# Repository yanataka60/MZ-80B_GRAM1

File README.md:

# MZ-80B GRAM1ボード

　MZ-80B OWNER'S MANUAL p65「図4-19 グラフィックメモリ1 MZ-8BG(オプション)」回路図から基板を起こしました。

　本体への装着方法は純正品と同じです。

## 回路図
　KiCadフォルダ内のMZ-80B_GRAM1.pdf参照

[回路図](https://github.com/yanataka60/MZ-80B_GRAM1/blob/main/KiCAD/MZ-80B_GRAM1.pdf)

## 部品表
|番号|品名|数量|備考|
| ------------ | ------------ | ------------ | ------------ |
|C1|電解コンデンサ 16V100uF|1||
|C2-C6, C8-C14, C16-C20|積層セラミックコンデンサ 0.1uF|17||
|C7|コンデンサ 470pF|1||
|C15|コンデンサ 220pF|1||
|J1|2x20ピンヘッダ|1|秋月電子通商 PH-2x40SG等|
|J2|2x5ピンヘッダ|2|秋月電子通商 PH-2x40SG等|
|J3|2x5ピンヘッダ|2|GRAM2接続用 秋月電子通商 PH-2x40SG等|
|R1-R4|カーボン抵抗 1k|4||
|R5|カーボン抵抗 47Ω|1||
|R6|カーボン抵抗 100Ω|1||
|U1|8kx8 SRAM 6264|1|若松通商等|
|U5-U8|74LS157|4|若松通商等|
|U10-U12|74LS93|3|若松通商等|
|U13|74LS245|1|若松通商等|
|U14|74LS165|1|若松通商等|
|U15|74LS175|1|若松通商等|
|U16|74LS04|1|若松通商等|
|U17|74LS107|1|若松通商等|
|U18, U20|74LS32|2|若松通商等|
|U19|74LS08|1|若松通商等|
|U21|74LS00|1|若松通商等|
||2x20フラットケーブル|1|15cm程度|
||2x5フラットケーブル|1|20cm程度|

## ボードの完成写真

## 取付方法
ケーブルは1Pinの△マークを合わせて接続します。マザーボート上で2x5Pinケーブルなら手前左に1Pinの△マークがあり、2x20Pinケーブルは、右奥に1Pinの△マークがあります。

上筐体の裏側にGRAM1ボードを挿し込みます。

## 追記
2025.10.10 回路図のpdfファイルを追加した。

2025.10.15 J3は使用しないので部品表を修正。

2025.10.16 すみません。GRAM2を使うときにはJ3必要でした。

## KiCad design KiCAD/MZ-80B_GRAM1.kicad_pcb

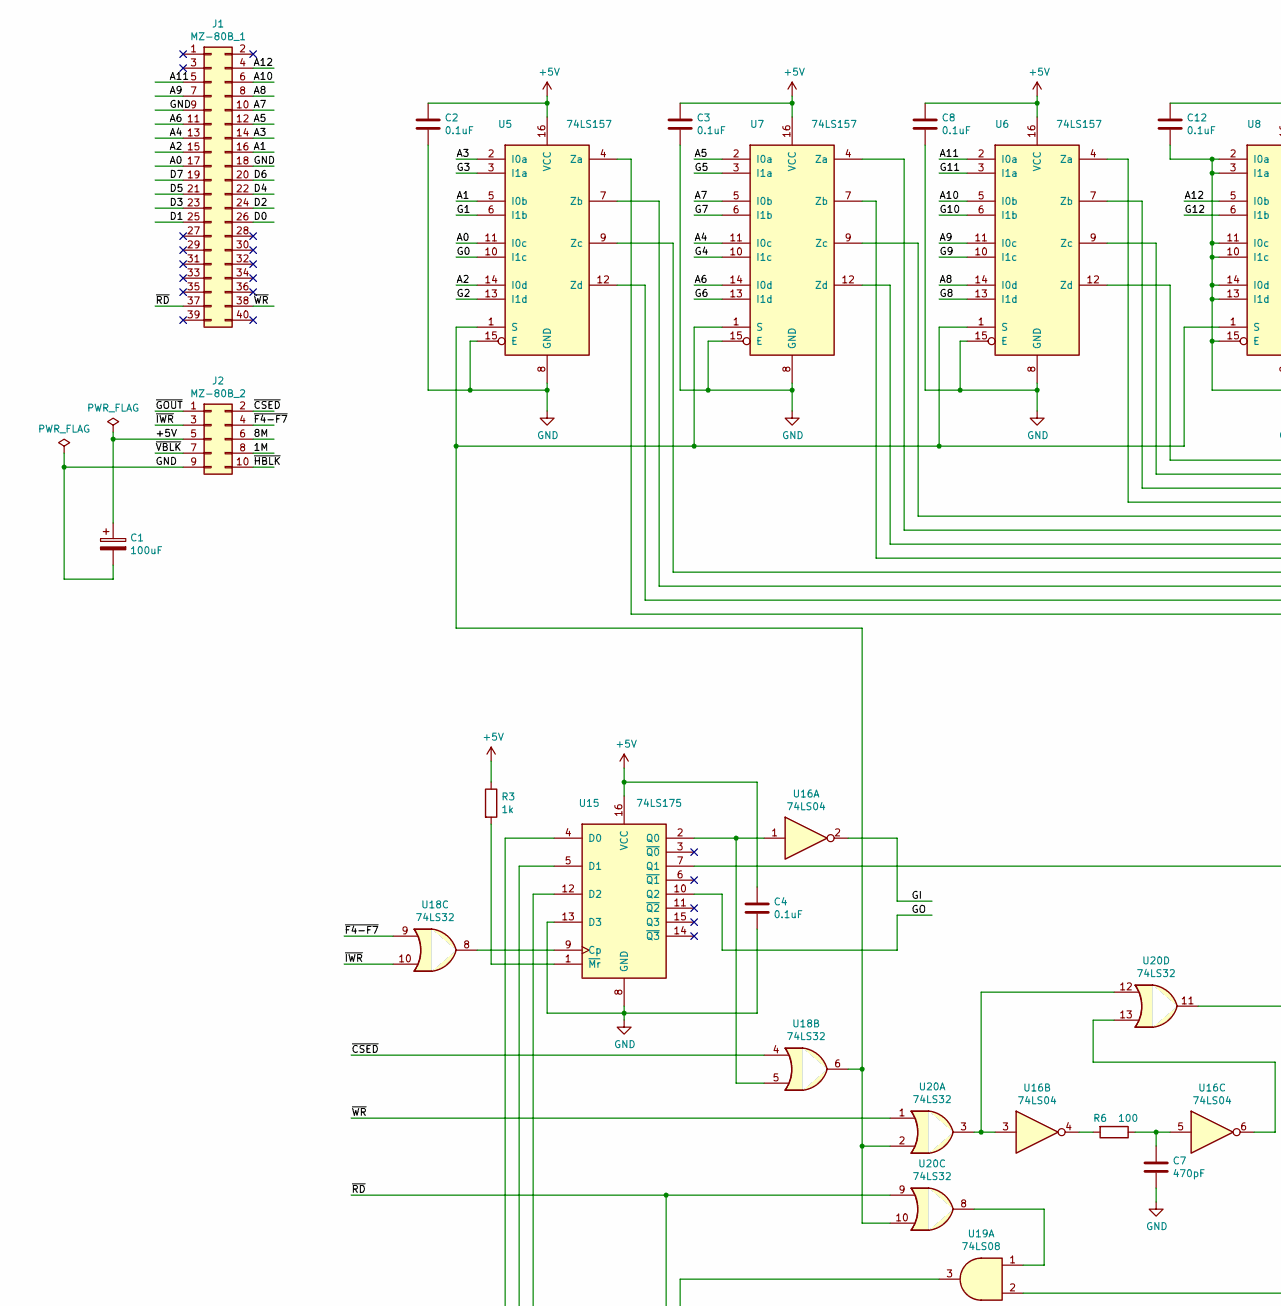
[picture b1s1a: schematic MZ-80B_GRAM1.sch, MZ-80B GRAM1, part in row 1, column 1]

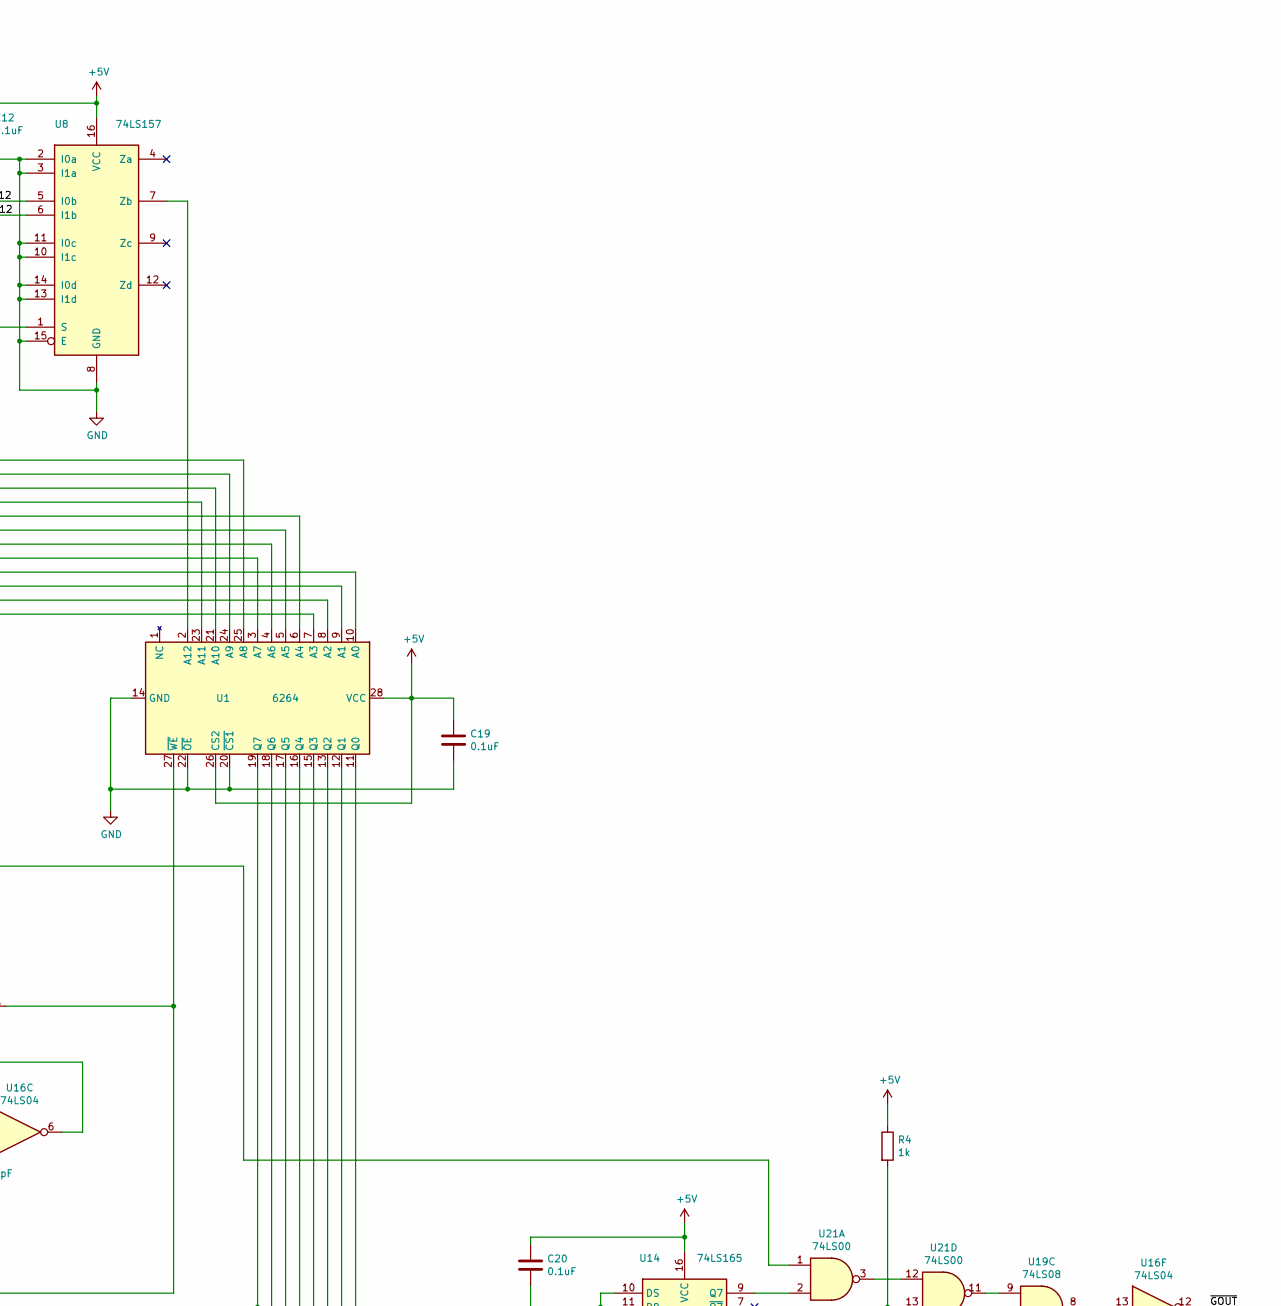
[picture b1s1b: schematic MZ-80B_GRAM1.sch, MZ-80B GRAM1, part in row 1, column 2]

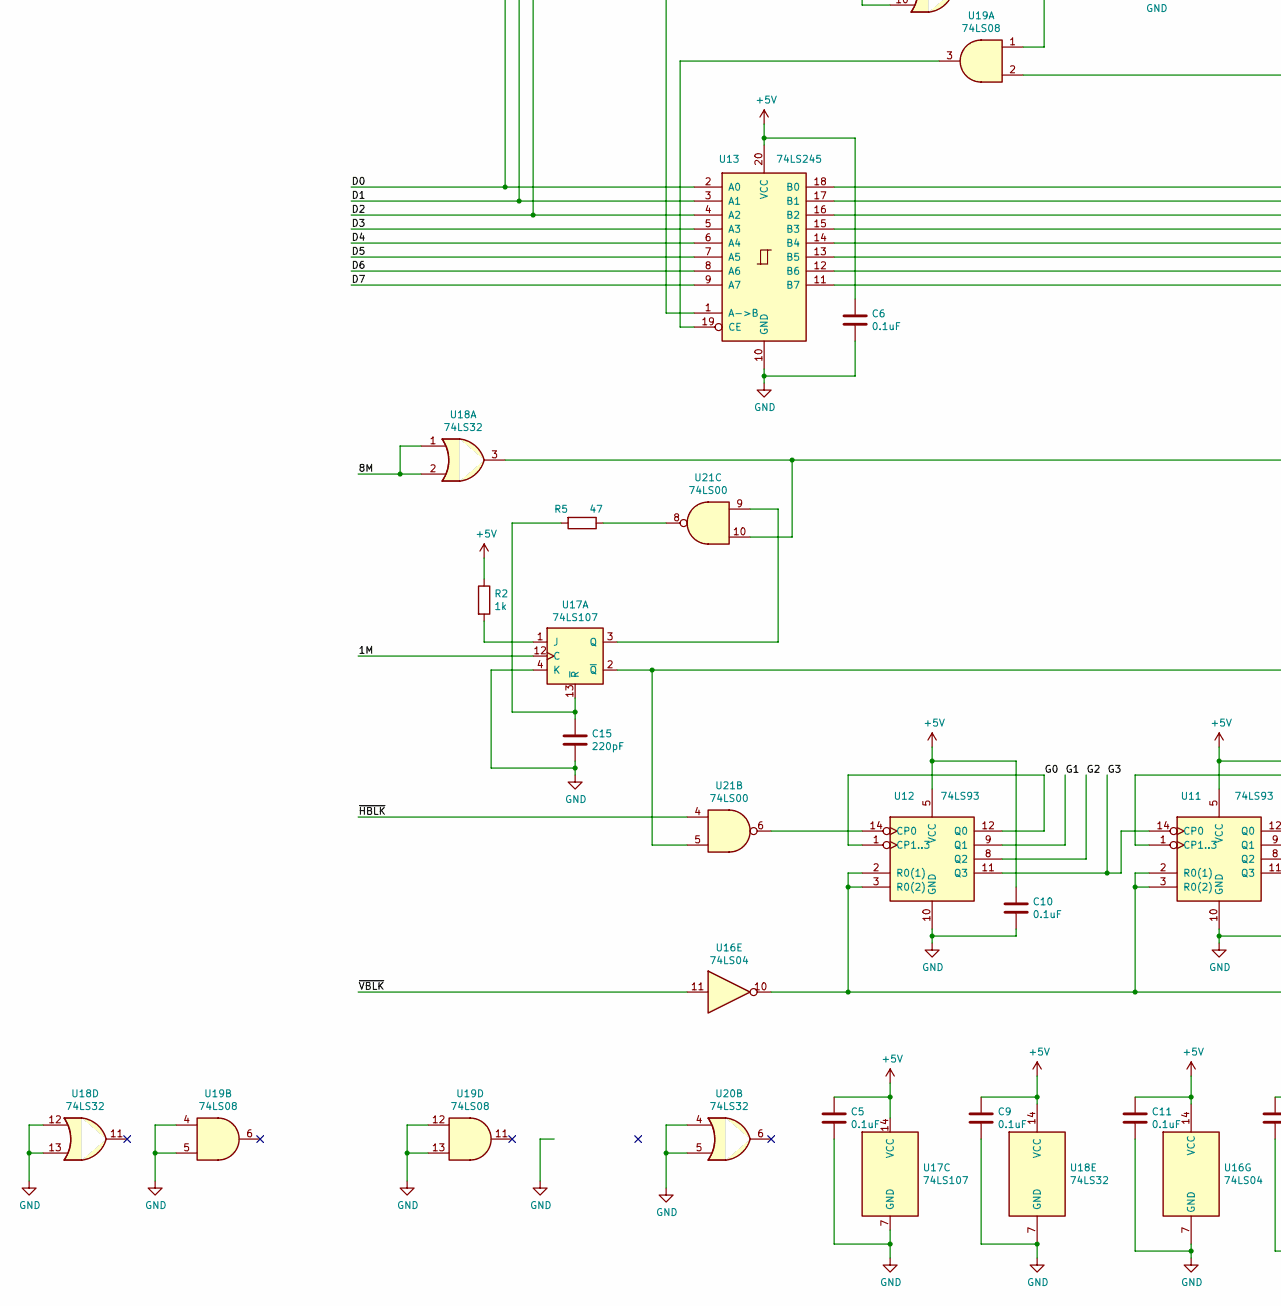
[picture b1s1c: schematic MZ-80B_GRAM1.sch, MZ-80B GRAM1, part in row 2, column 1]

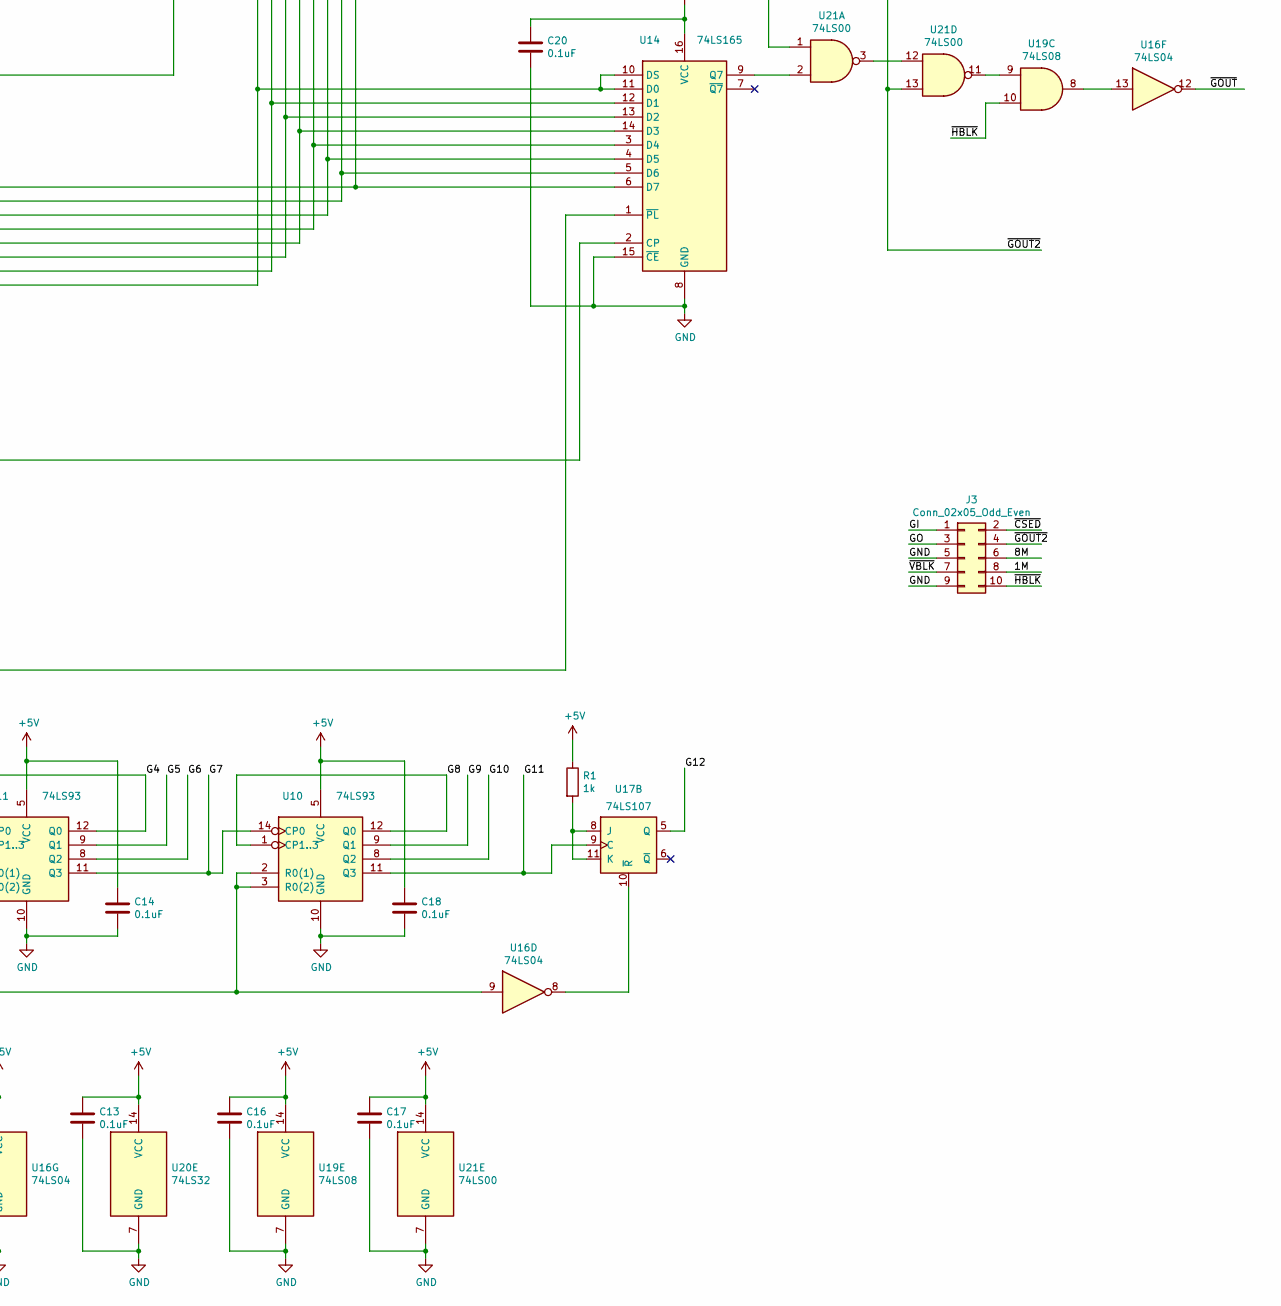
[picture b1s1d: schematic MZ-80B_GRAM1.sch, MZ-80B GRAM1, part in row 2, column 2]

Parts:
C1: 100uF; CP_Radial_D5.0mm_P2.50mm
C2, C3, C4, C5, C6, C8, C9, C10, C11, C12, C13, C14, C16, C17, C18, C19, C20: 0.1uF; C_Rect_L4.0mm_W2.5mm_P2.50mm
C7: 470pF; C_Rect_L4.0mm_W2.5mm_P2.50mm
C15: 220pF; C_Rect_L4.0mm_W2.5mm_P2.50mm
J1: MZ-80B_1; PinHeader_2x20_P2.54mm_Vertical
J2: MZ-80B_2; PinHeader_2x05_P2.54mm_Vertical
J3: Conn_02x05_Odd_Even; PinHeader_2x05_P2.54mm_Vertical
R1, R2, R3, R4: 1k; R_Axial_DIN0207_L6.3mm_D2.5mm_P7.62mm_Horizontal
R5: 47; R_Axial_DIN0207_L6.3mm_D2.5mm_P7.62mm_Horizontal
R6: 100; R_Axial_DIN0207_L6.3mm_D2.5mm_P7.62mm_Horizontal
U1: 6264; DIP-28_W15.24mm_LongPads
U5, U6, U7, U8: 74LS157; DIP-16_W7.62mm_LongPads
U10, U11, U12: 74LS93; DIP-14_W7.62mm_LongPads
U13: 74LS245; DIP-20_W7.62mm_LongPads
U14: 74LS165; DIP-16_W7.62mm_LongPads
U15: 74LS175; DIP-16_W7.62mm_LongPads
U16: 74LS04; DIP-14_W7.62mm_LongPads
U17: 74LS107; DIP-14_W7.62mm_LongPads
U18, U20: 74LS32; DIP-14_W7.62mm_LongPads
U19: 74LS08; DIP-14_W7.62mm_LongPads
U21: 74LS00; DIP-14_W7.62mm_LongPads

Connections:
+5V: C1.1, C2.1, C3.1, C4.1, C5.1, C6.1, C8.1, C9.1, C10.1, C11.1, C12.1, C13.1, C14.1, C16.1, C17.1, C18.1, C19.1, C20.1, J2.5, R1.1, R2.1, R3.1, R4.1, U1.26 (CS2), U1.28 (VCC), U5.16 (VCC), U6.16 (VCC), U7.16 (VCC), U8.16 (VCC), U10.5 (VCC), U11.5 (VCC), U12.5 (VCC), U13.20 (VCC), U14.16 (VCC), U15.16 (VCC), U16.14 (VCC), U17.14 (VCC), U18.14 (VCC), U19.14 (VCC), U20.14 (VCC), U21.14 (VCC)
/1M: J2.8, J3.8, U17.12 (C)
/8M: J2.6, J3.6, U18.1, U18.2
/A0: J1.17, U5.11 (I0c)
/A1: J1.16, U5.5 (I0b)
/A2: J1.15, U5.14 (I0d)
/A3: J1.14, U5.2 (I0a)
/A4: J1.13, U7.11 (I0c)
/A5: J1.12, U7.2 (I0a)
/A6: J1.11, U7.14 (I0d)
/A7: J1.10, U7.5 (I0b)
/A8: J1.8, U6.14 (I0d)
/A9: J1.7, U6.11 (I0c)
/A10: J1.6, U6.5 (I0b)
/A11: J1.5, U6.2 (I0a)
/A12: J1.4, U8.5 (I0b)
/D0: J1.26, U13.2 (A0), U15.4 (D0)
/D1: J1.25, U13.3 (A1), U15.5 (D1)
/D2: J1.24, U13.4 (A2), U15.12 (D2)
/D3: J1.23, U13.5 (A3)
/D4: J1.22, U13.6 (A4)
/D5: J1.21, U13.7 (A5)
/D6: J1.20, U13.8 (A6)
/D7: J1.19, U13.9 (A7)
/G0: U5.10 (I1c), U12.1 (CP1..3), U12.12 (Q0)
/G1: U5.6 (I1b), U12.9 (Q1)
/G2: U5.13 (I1d), U12.8 (Q2)
/G3: U5.3 (I1a), U11.14 (CP0), U12.11 (Q3)
/G4: U7.10 (I1c), U11.1 (CP1..3), U11.12 (Q0)
/G5: U7.3 (I1a), U11.9 (Q1)
/G6: U7.13 (I1d), U11.8 (Q2)
/G7: U7.6 (I1b), U10.14 (CP0), U11.11 (Q3)
/G8: U6.13 (I1d), U10.1 (CP1..3), U10.12 (Q0)
/G9: U6.10 (I1c), U10.9 (Q1)
/G10: U6.6 (I1b), U10.8 (Q2)
/G11: U6.3 (I1a), U10.11 (Q3), U17.9 (C)
/G12: U8.6 (I1b), U17.5 (Q)
/GI: J3.1, U16.2
/GO: J3.3, U15.10 (Q2)
/~CSED: J2.2, J3.2, U18.4
/~F4-F7: J2.4, U18.9
/~GOUT: J2.1, U16.12
/~GOUT2: J3.4, R4.2, U21.13
/~HBLK: J2.10, J3.10, U19.10, U21.4
/~IWR: J2.3, U18.10
/~RD: J1.37, U13.1 (A->B), U20.9
/~VBLK: J2.7, J3.7, U16.11
/~WR: J1.38, U20.1
GND: C1.2, C2.2, C3.2, C4.2, C5.2, C6.2, C7.2, C8.2, C9.2, C10.2, C11.2, C12.2, C13.2, C14.2, C15.2, C16.2, C17.2, C18.2, C19.2, C20.2, J1.9, J1.18, J2.9, J3.5, J3.9, U1.14 (GND), U1.20 (~CS1), U1.22 (~OE), U5.8 (GND), U5.15 (E), U6.8 (GND), U6.15 (E), U7.8 (GND), U7.15 (E), U8.2 (I0a), U8.3 (I1a), U8.8 (GND), U8.10 (I1c), U8.11 (I0c), U8.13 (I1d), U8.14 (I0d), U8.15 (E), U10.10 (GND), U11.10 (GND), U12.10 (GND), U13.10 (GND), U14.8 (GND), U14.15 (~CE), U15.8 (GND), U15.13 (D3), U16.7 (GND), U17.4 (K), U17.7 (GND), U18.7 (GND), U18.12, U18.13, U19.4, U19.5, U19.7 (GND), U19.12, U19.13, U20.4, U20.5, U20.7 (GND), U21.7 (GND)
unnamed: C7.1, R6.1, U16.5
unnamed: C15.1, R5.2, U17.13 (~R)
unnamed: R1.2, U17.8 (J), U17.11 (K)
unnamed: R2.2, U17.1 (J)
unnamed: R3.2, U15.1 (~Mr)
unnamed: R5.1, U21.8
unnamed: R6.2, U16.4
unnamed: U1.2 (A12), U8.7 (Zb)
unnamed: U1.3 (A7), U7.7 (Zb)
unnamed: U1.4 (A6), U7.12 (Zd)
unnamed: U1.5 (A5), U7.4 (Za)
unnamed: U1.6 (A4), U7.9 (Zc)
unnamed: U1.7 (A3), U5.4 (Za)
unnamed: U1.8 (A2), U5.12 (Zd)
unnamed: U1.9 (A1), U5.7 (Zb)
unnamed: U1.10 (A0), U5.9 (Zc)
unnamed: U1.11 (Q0), U13.18 (B0), U14.6 (D7)
unnamed: U1.12 (Q1), U13.17 (B1), U14.5 (D6)
unnamed: U1.13 (Q2), U13.16 (B2), U14.4 (D5)
unnamed: U1.15 (Q3), U13.15 (B3), U14.3 (D4)
unnamed: U1.16 (Q4), U13.14 (B4), U14.14 (D3)
unnamed: U1.17 (Q5), U13.13 (B5), U14.13 (D2)
unnamed: U1.18 (Q6), U13.12 (B6), U14.12 (D1)
unnamed: U1.19 (Q7), U13.11 (B7), U14.10 (DS), U14.11 (D0)
unnamed: U1.21 (A10), U6.7 (Zb)
unnamed: U1.23 (A11), U6.4 (Za)
unnamed: U1.24 (A9), U6.9 (Zc)
unnamed: U1.25 (A8), U6.12 (Zd)
unnamed: U1.27 (~WE), U19.2, U20.11
unnamed: U10.2 (R0(1)), U10.3 (R0(2)), U11.2 (R0(1)), U11.3 (R0(2)), U12.2 (R0(1)), U12.3 (R0(2)), U16.9, U16.10
unnamed: U12.14 (CP0), U21.6
unnamed: U13.19 (CE), U19.3
unnamed: U14.1 (~PL), U17.2 (~Q), U21.5
unnamed: U14.2 (CP), U18.3, U21.10
unnamed: U14.9 (Q7), U21.2
unnamed: U15.2 (Q0), U16.1, U18.5
unnamed: U15.7 (Q1), U21.1
unnamed: U15.9 (Cp), U18.8
unnamed: U16.3, U20.3, U20.12
unnamed: U16.6, U20.13
unnamed: U16.8, U17.10 (~R)
unnamed: U16.13, U19.8
unnamed: U17.3 (Q), U21.9
unnamed: U5.1 (S), U6.1 (S), U7.1 (S), U8.1 (S), U18.6, U20.2, U20.10
unnamed: U19.1, U20.8
unnamed: U19.9, U21.11
unnamed: U21.3, U21.12

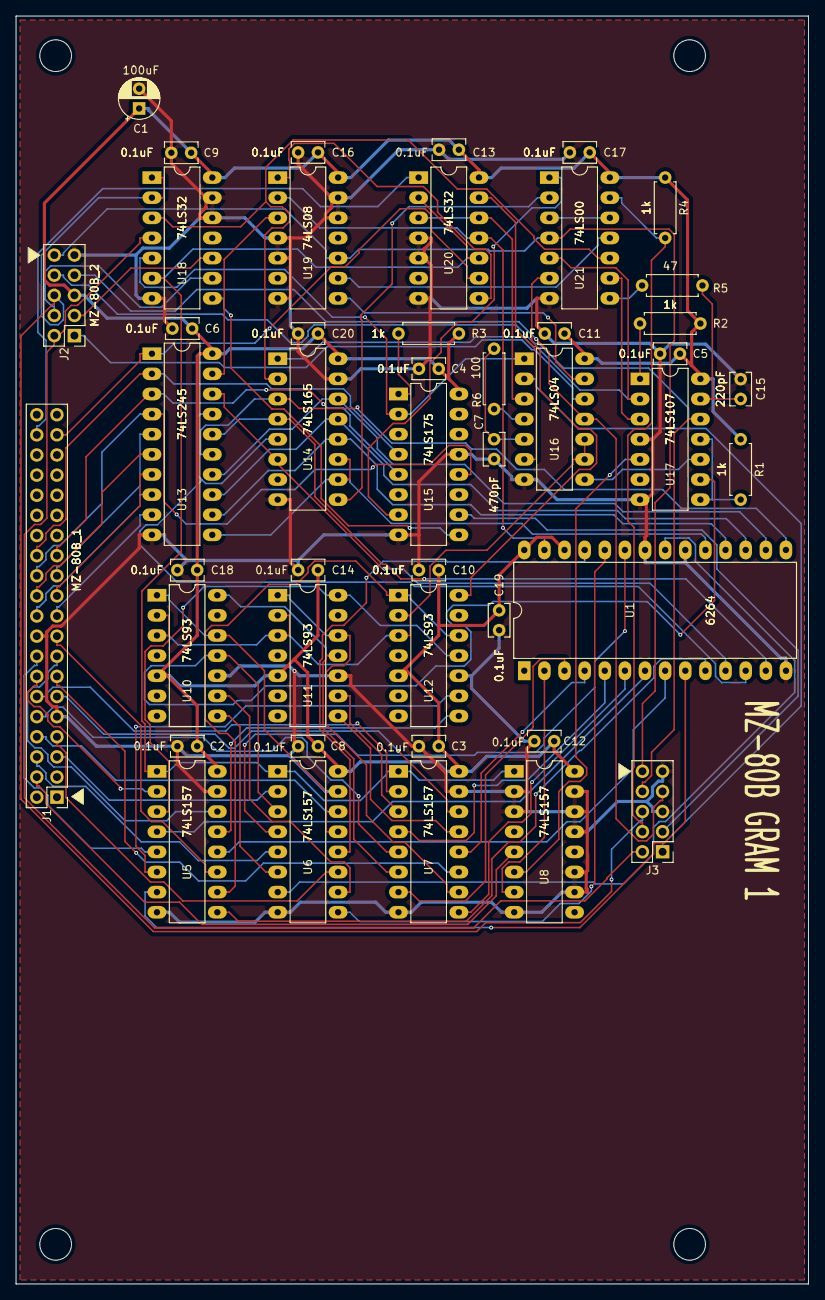
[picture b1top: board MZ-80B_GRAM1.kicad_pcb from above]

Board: 2 copper layers, 100.0 x 160.0 mm, 50 parts (0 on the bottom side), 96 nets.

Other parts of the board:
MH1, MH2, MH3, MH4: MountingHole_4mm
